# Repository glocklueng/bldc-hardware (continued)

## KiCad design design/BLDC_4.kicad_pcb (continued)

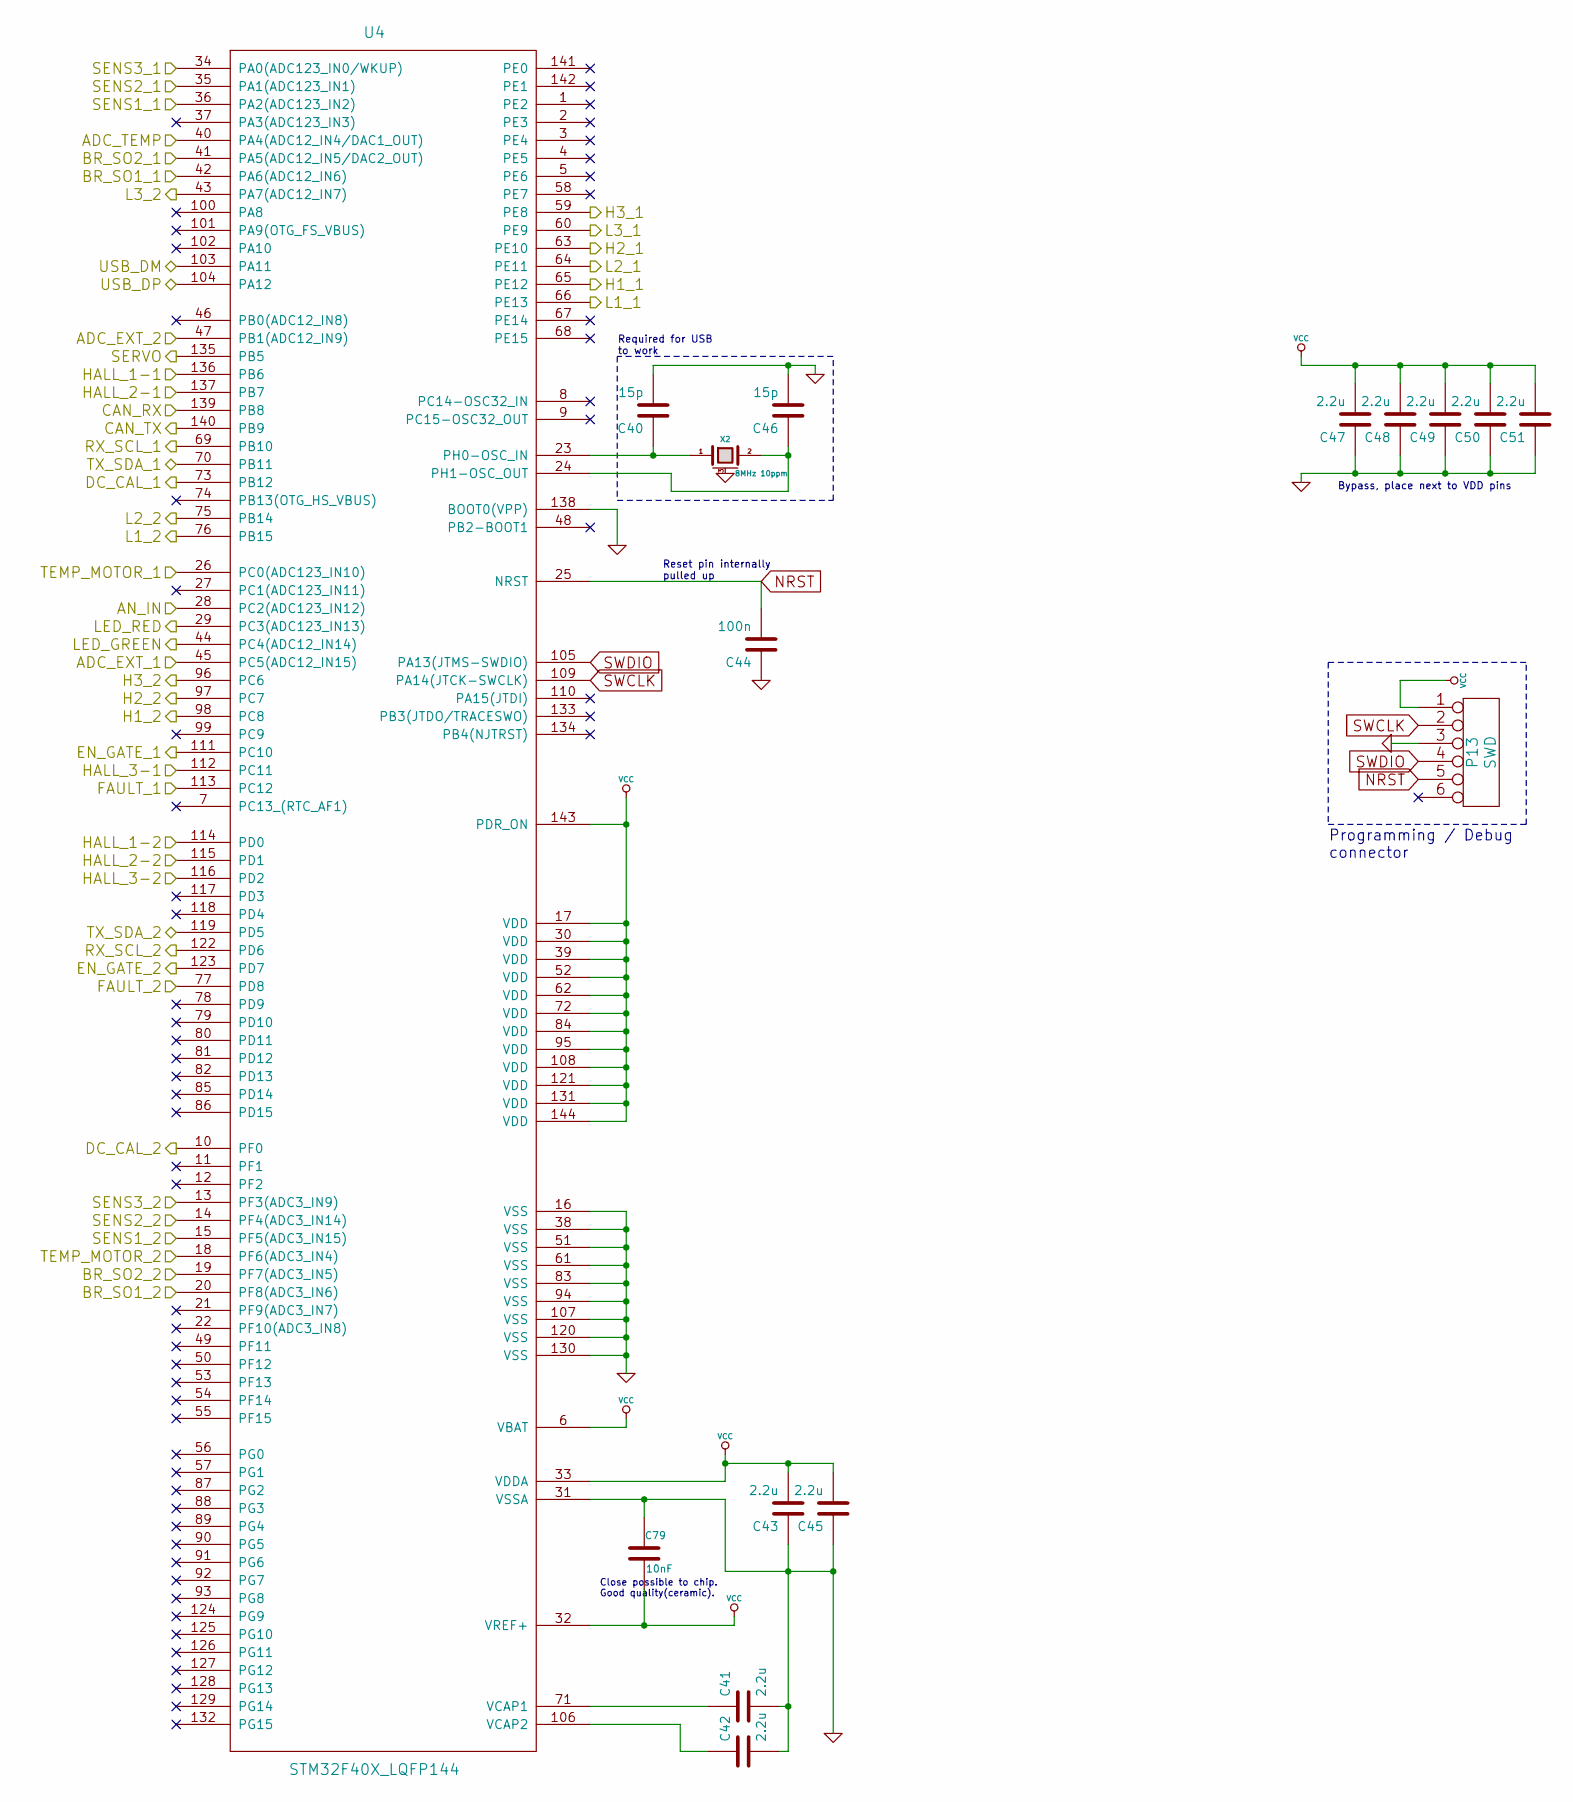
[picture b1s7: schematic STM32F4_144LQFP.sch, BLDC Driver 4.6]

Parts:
C40, C46: 15p; SMD-0603_c
C41, C42, C43, C45, C47, C48, C49, C50, C51: 2.2u; SMD-0603_c
C44: 100n; SMD-0603_c
C79: 10nF; SMD-0603_c
P13: SWD; MICRO_JST_6
U4: STM32F40X_LQFP144; TQFP-144_20x20mm_Pitch0.5mm
X2: 8MHz 10ppm; Crystal_5x3mm; mfg# ABM3B-8.0-10-1UT

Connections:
/CAN bus transceiver/CAN_RX: U4.139 (PB8); also elsewhere on the board
/CAN bus transceiver/CAN_TX: U4.140 (PB9); also elsewhere on the board
/Filters/HALL1_OUT: U4.136 (PB6); also elsewhere on the board
/Filters/HALL2_OUT: U4.137 (PB7); also elsewhere on the board
/Filters/HALL3_OUT: U4.112 (PC11); also elsewhere on the board
/Filters/TEMP_IN: U4.26 (PC0(ADC123_IN10)); also elsewhere on the board
/Filters_2/HALL1_OUT: U4.114 (PD0); also elsewhere on the board
/Filters_2/HALL2_OUT: U4.115 (PD1); also elsewhere on the board
/Filters_2/HALL3_OUT: U4.116 (PD2); also elsewhere on the board
/Filters_2/TEMP_IN: U4.18 (PF6(ADC3_IN4)); also elsewhere on the board
/MCU/ADC_EXT_1: U4.45 (PC5(ADC12_IN15)); also elsewhere on the board
/MCU/ADC_EXT_2: U4.47 (PB1(ADC12_IN9)); also elsewhere on the board
/MCU/ADC_TEMP: U4.40 (PA4(ADC12_IN4/DAC1_OUT)); also elsewhere on the board
/MCU/AN_IN: U4.28 (PC2(ADC123_IN12)); also elsewhere on the board
/MCU/LED_GREEN: U4.44 (PC4(ADC12_IN14)); also elsewhere on the board
/MCU/LED_RED: U4.29 (PC3(ADC123_IN13)); also elsewhere on the board
/MCU/RX_SCL_1: U4.69 (PB10); also elsewhere on the board
/MCU/RX_SCL_2: U4.122 (PD6); also elsewhere on the board
/MCU/SERVO: U4.135 (PB5); also elsewhere on the board
/MCU/TX_SDA_1: U4.70 (PB11); also elsewhere on the board
/MCU/TX_SDA_2: U4.119 (PD5); also elsewhere on the board
/MCU/USB_DM: U4.103 (PA11); also elsewhere on the board
/MCU/USB_DP: U4.104 (PA12); also elsewhere on the board
/Mosfet driver/BR_SO1: U4.42 (PA6(ADC12_IN6)); also elsewhere on the board
/Mosfet driver/BR_SO2: U4.41 (PA5(ADC12_IN5/DAC2_OUT)); also elsewhere on the board
/Mosfet driver/DC_CAL: U4.73 (PB12); also elsewhere on the board
/Mosfet driver/EN_GATE: U4.111 (PC10); also elsewhere on the board
/Mosfet driver/FAULT: U4.113 (PC12); also elsewhere on the board
/Mosfet driver/H1: U4.65 (PE12); also elsewhere on the board
/Mosfet driver/H2: U4.63 (PE10); also elsewhere on the board
/Mosfet driver/H3: U4.59 (PE8); also elsewhere on the board
/Mosfet driver/L1: U4.66 (PE13); also elsewhere on the board
/Mosfet driver/L2: U4.64 (PE11); also elsewhere on the board
/Mosfet driver/L3: U4.60 (PE9); also elsewhere on the board
/Mosfet driver/SENS1: U4.36 (PA2(ADC123_IN2)); also elsewhere on the board
/Mosfet driver/SENS2: U4.35 (PA1(ADC123_IN1)); also elsewhere on the board
/Mosfet driver/SENS3: U4.34 (PA0(ADC123_IN0/WKUP)); also elsewhere on the board
/Mosfet driver_2/BR_SO1: U4.20 (PF8(ADC3_IN6)); also elsewhere on the board
/Mosfet driver_2/BR_SO2: U4.19 (PF7(ADC3_IN5)); also elsewhere on the board
/Mosfet driver_2/DC_CAL: U4.10 (PF0); also elsewhere on the board
/Mosfet driver_2/EN_GATE: U4.123 (PD7); also elsewhere on the board
/Mosfet driver_2/FAULT: U4.77 (PD8); also elsewhere on the board
/Mosfet driver_2/H1: U4.98 (PC8); also elsewhere on the board
/Mosfet driver_2/H2: U4.97 (PC7); also elsewhere on the board
/Mosfet driver_2/H3: U4.96 (PC6); also elsewhere on the board
/Mosfet driver_2/L1: U4.76 (PB15); also elsewhere on the board
/Mosfet driver_2/L2: U4.75 (PB14); also elsewhere on the board
/Mosfet driver_2/L3: U4.43 (PA7(ADC12_IN7)); also elsewhere on the board
/Mosfet driver_2/SENS1: U4.15 (PF5(ADC3_IN15)); also elsewhere on the board
/Mosfet driver_2/SENS2: U4.14 (PF4(ADC3_IN14)); also elsewhere on the board
/Mosfet driver_2/SENS3: U4.13 (PF3(ADC3_IN9)); also elsewhere on the board
GND: C40.2, C41.2, C42.2, C43.1, C44.1, C45.1, C46.2, C47.1, C48.1, C49.1, C50.1, C51.1, C79.1, P13.3, U4.16 (VSS), U4.31 (VSSA), U4.38 (VSS), U4.51 (VSS), U4.61 (VSS), U4.83 (VSS), U4.94 (VSS), U4.107 (VSS), U4.120 (VSS), U4.130 (VSS), U4.138 (BOOT0(VPP)), X2.3 (case); also elsewhere on the board
NRST: C44.2, P13.5, U4.25 (NRST)
unnamed: C40.1, U4.23 (PH0-OSC_IN), X2.1
unnamed: C41.1, U4.71 (VCAP1)
unnamed: C42.1, U4.106 (VCAP2)
unnamed: C46.1, U4.24 (PH1-OSC_OUT), X2.2
SWCLK: P13.2, U4.109 (PA14(JTCK-SWCLK))
SWDIO: P13.4, U4.105 (PA13(JTMS-SWDIO))
VCC: C43.2, C45.2, C47.2, C48.2, C49.2, C50.2, C51.2, C79.2, P13.1, U4.6 (VBAT), U4.17 (VDD), U4.30 (VDD), U4.32 (VREF+), U4.33 (VDDA), U4.39 (VDD), U4.52 (VDD), U4.62 (VDD), U4.72 (VDD), U4.84 (VDD), U4.95 (VDD), U4.108 (VDD), U4.121 (VDD), U4.131 (VDD), U4.143 (PDR_ON), U4.144 (VDD); also elsewhere on the board

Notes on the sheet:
Programming / Debug connector
Reset pin internally pulled up
Required for USB to work
Bypass, place next to VDD pins
Close possible to chip. Good quality(ceramic).

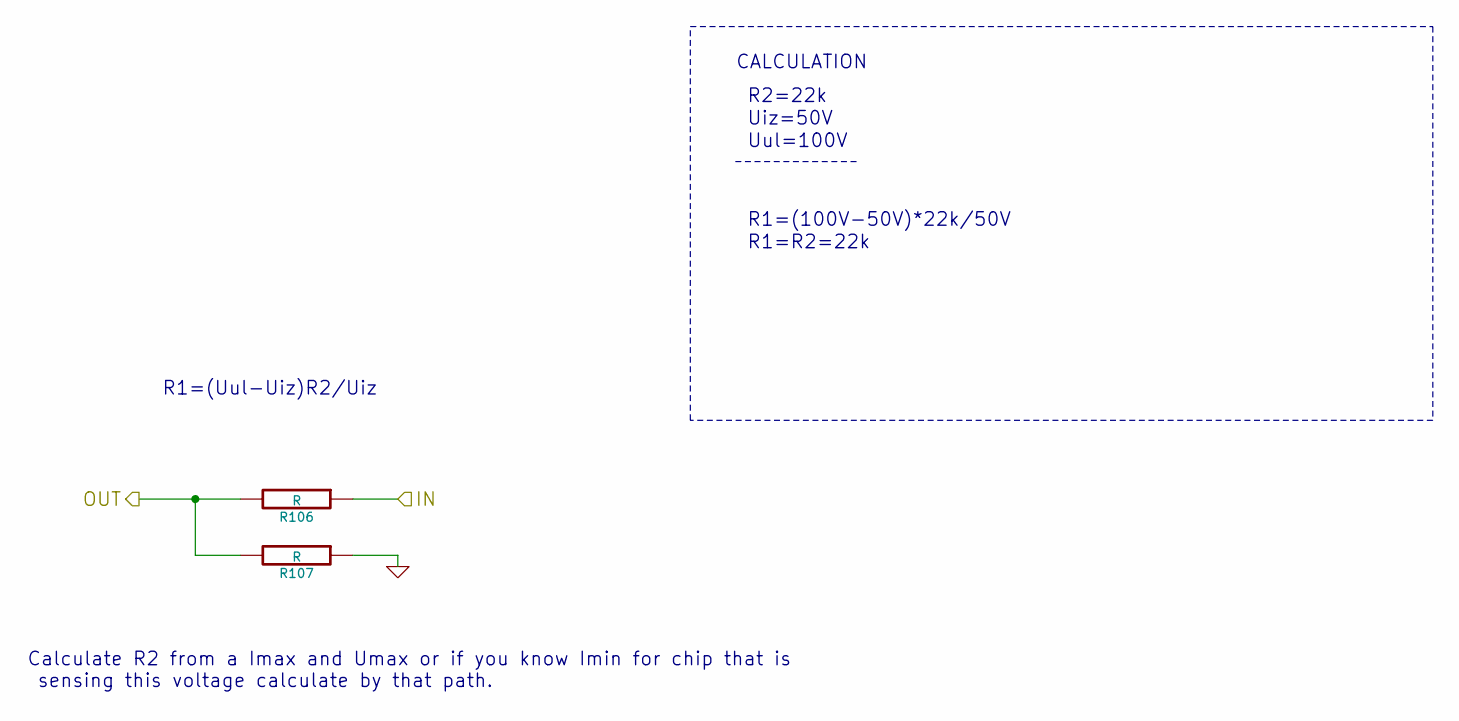
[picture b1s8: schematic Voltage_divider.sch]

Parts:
R92, R93: R

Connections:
/Mosfet driver/Voltage_divider.sch/OUT: R92.2, R93.2; also elsewhere on the board
GND: R93.1; also elsewhere on the board

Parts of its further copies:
R86, R87, R88, R89, R90, R91, R94, R95, R96, R97, R98, R99, R100, R101, R102, R103, R104, R105, R106, R107, R108, R109: R

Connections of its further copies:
/Mosfet driver/H3_VS: R90.1; also elsewhere on the board
/Mosfet driver/Voltage_divider.sch/OUT: R86.2, R87.2, R88.2, R89.2, R90.2, R91.2, R94.2, R95.2, R96.2, R97.2; also elsewhere on the board
/Mosfet driver_2/H3_VS: R102.1; also elsewhere on the board
/Mosfet driver_2/Voltage_divider.sch/OUT: R98.2, R99.2, R100.2, R101.2, R102.2, R103.2, R104.2, R105.2, R106.2, R107.2, R108.2, R109.2; also elsewhere on the board
GND: R87.1, R89.1, R91.1, R94.1, R95.1, R97.1, R99.1, R101.1, R103.1, R105.1, R106.1, R107.1, R109.1; also elsewhere on the board

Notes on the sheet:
R1=(Uul-Uiz)R2/Uiz
Calculate R2 from a Imax and Umax or if you know Imin for chip that is sensing this voltage calculate by that path.
CALCULATION
R2=22k
Uiz=50V
Uul=100V
R1=(100V-50V)*22k/50V
R1=R2=22k

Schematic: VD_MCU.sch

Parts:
R46, R47: R

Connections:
/Mosfet driver/H3_VS: R46.1; also elsewhere on the board
/Mosfet driver/SENS1: R46.2, R47.2; also elsewhere on the board
GND: R47.1; also elsewhere on the board

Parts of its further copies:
R48, R49, R50, R51, R80, R81, R82, R83, R84, R85: R

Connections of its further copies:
/Mosfet driver/SENS2: R48.2, R49.2; also elsewhere on the board
/Mosfet driver/SENS3: R50.2, R51.2; also elsewhere on the board
/Mosfet driver_2/H3_VS: R80.1; also elsewhere on the board
/Mosfet driver_2/SENS1: R80.2, R81.2; also elsewhere on the board
/Mosfet driver_2/SENS2: R82.2, R83.2; also elsewhere on the board
/Mosfet driver_2/SENS3: R84.2, R85.2; also elsewhere on the board
GND: R49.1, R51.1, R81.1, R83.1, R85.1; also elsewhere on the board

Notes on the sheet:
Voltage divider for MCU, equtions same as for Volatage_divider. For Uul=100V, Uiz=4.78V~5V and R2=2.9k R1=58k

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
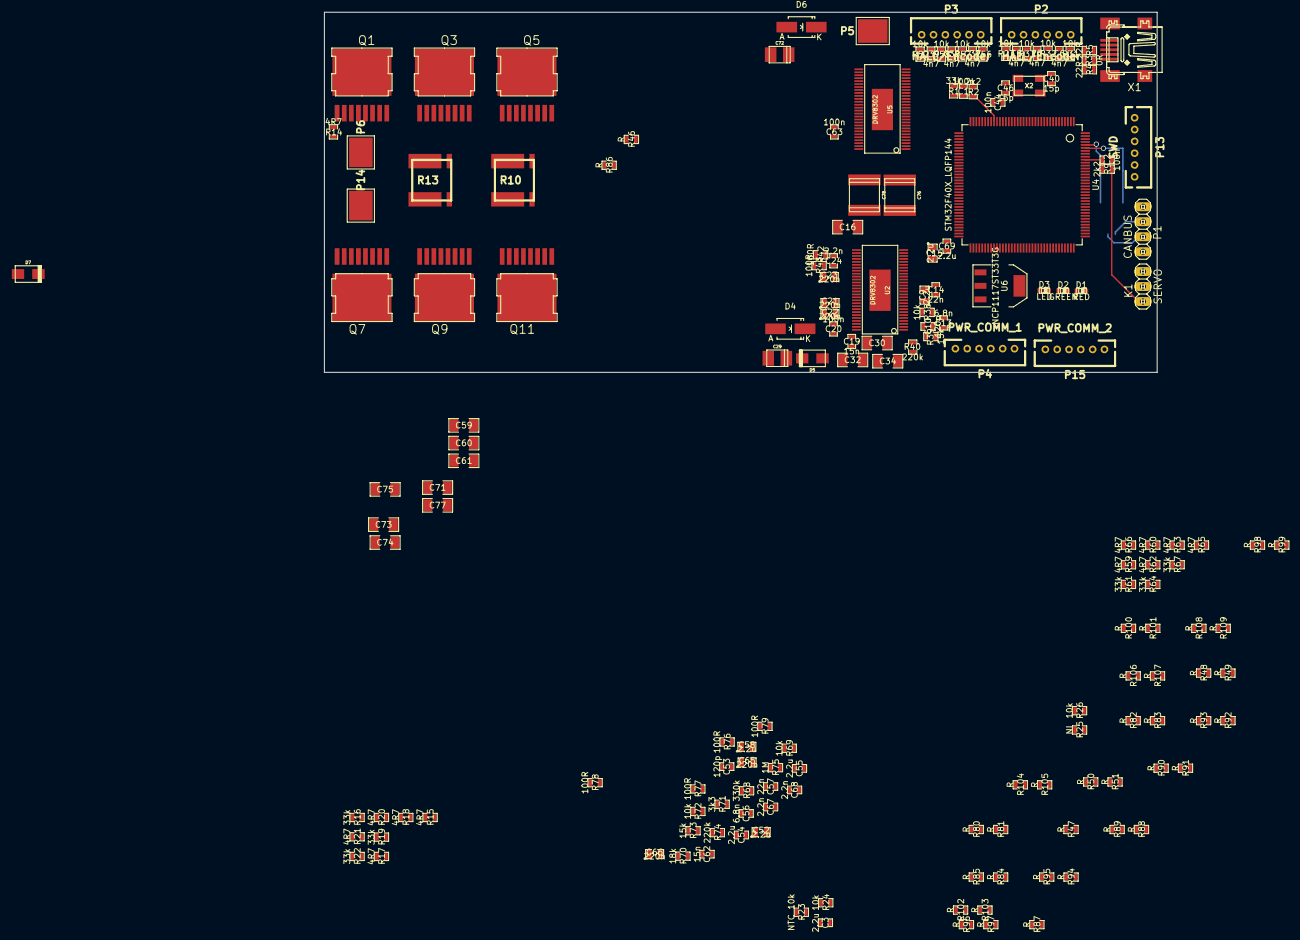
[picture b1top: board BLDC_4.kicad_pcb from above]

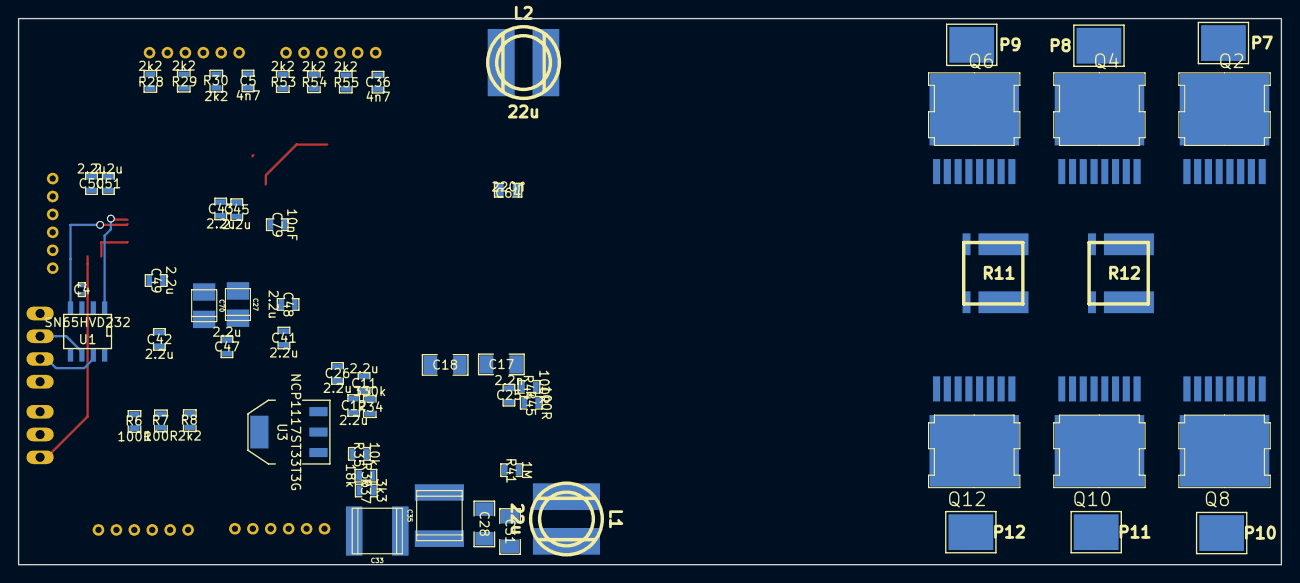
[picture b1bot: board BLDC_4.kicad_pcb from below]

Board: 4 copper layers, 141.0 x 61.0 mm, 233 parts (60 on the bottom side), 167 nets.

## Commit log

2015-01-09 Add a datasheet + all doc for STM microcontroller so i can add a bigger 144-pins version and also now how to work with it
2015-01-09 Add some MOSFET's tha could be good for our project
2015-01-09 rename a file so ican know what i'am opening
2015-01-09 Add a new 144pins MCU
2015-01-09 Last not commitied file
2015-01-10 Some small fixups in lib
2015-01-10 Some small changes so i can understand and see better
2015-01-10 Add a new 144 to schematic and start working on it
2015-01-10 Remove uneded .pro file
2015-01-13 Add a electronic for second motor and add new pin's for it on MCU; TODO Add new mosfets
2015-01-16 Make a BOM + change .cmp so components match mine's libs
2015-01-16 PS plot of scheme
2015-01-16 Plot of schemas in one pdf
2015-01-16 Make change in annotations and some small fixes
2015-01-16 Change names of sheets so there's no erc warnings, add pdf in color
2015-01-22 Change sheet for college and som in pdf
2015-02-06 Add a voltage divider resistors for driver chip
2015-02-06 Declare mosfet supply
2015-02-08 Change libraries ot new pretty format
2015-02-10 Sane lib configuration
2015-02-11 Fix libraries
2015-02-13 Add pwr for second motor
2015-02-13 Voltage divider for DRV and MCU
2015-02-13 Update pdf's and ps
2015-02-13 Fix some ERC error, add decoupling cap to Vref+ and make some small changes to lib
2015-02-14 Start pcb
2015-02-14 Remove lib temp
2015-02-14 Fix libs
2015-02-14 Add led's lib
2015-02-14 Chnge name of crf lib and add footprint for new cap
2015-02-16 Some fixes in libs,schemas and netlist. Start new PCB
2015-02-16 Footprint for mosfets and change them in schematics and in netlist
2015-02-16 Start work on pcb
2015-02-17 Layout all on pcb except some resitors
2015-02-17 Add all components
2015-02-17 Routing ... Maybe H_VS and other dividers are to close to chip and one another it's a 100V.
2015-02-25 New pcb layout
2015-03-04 New desing starting placment of components
2015-03-07 More layouting
2015-05-14 Add a new driver this time and for IGBT
